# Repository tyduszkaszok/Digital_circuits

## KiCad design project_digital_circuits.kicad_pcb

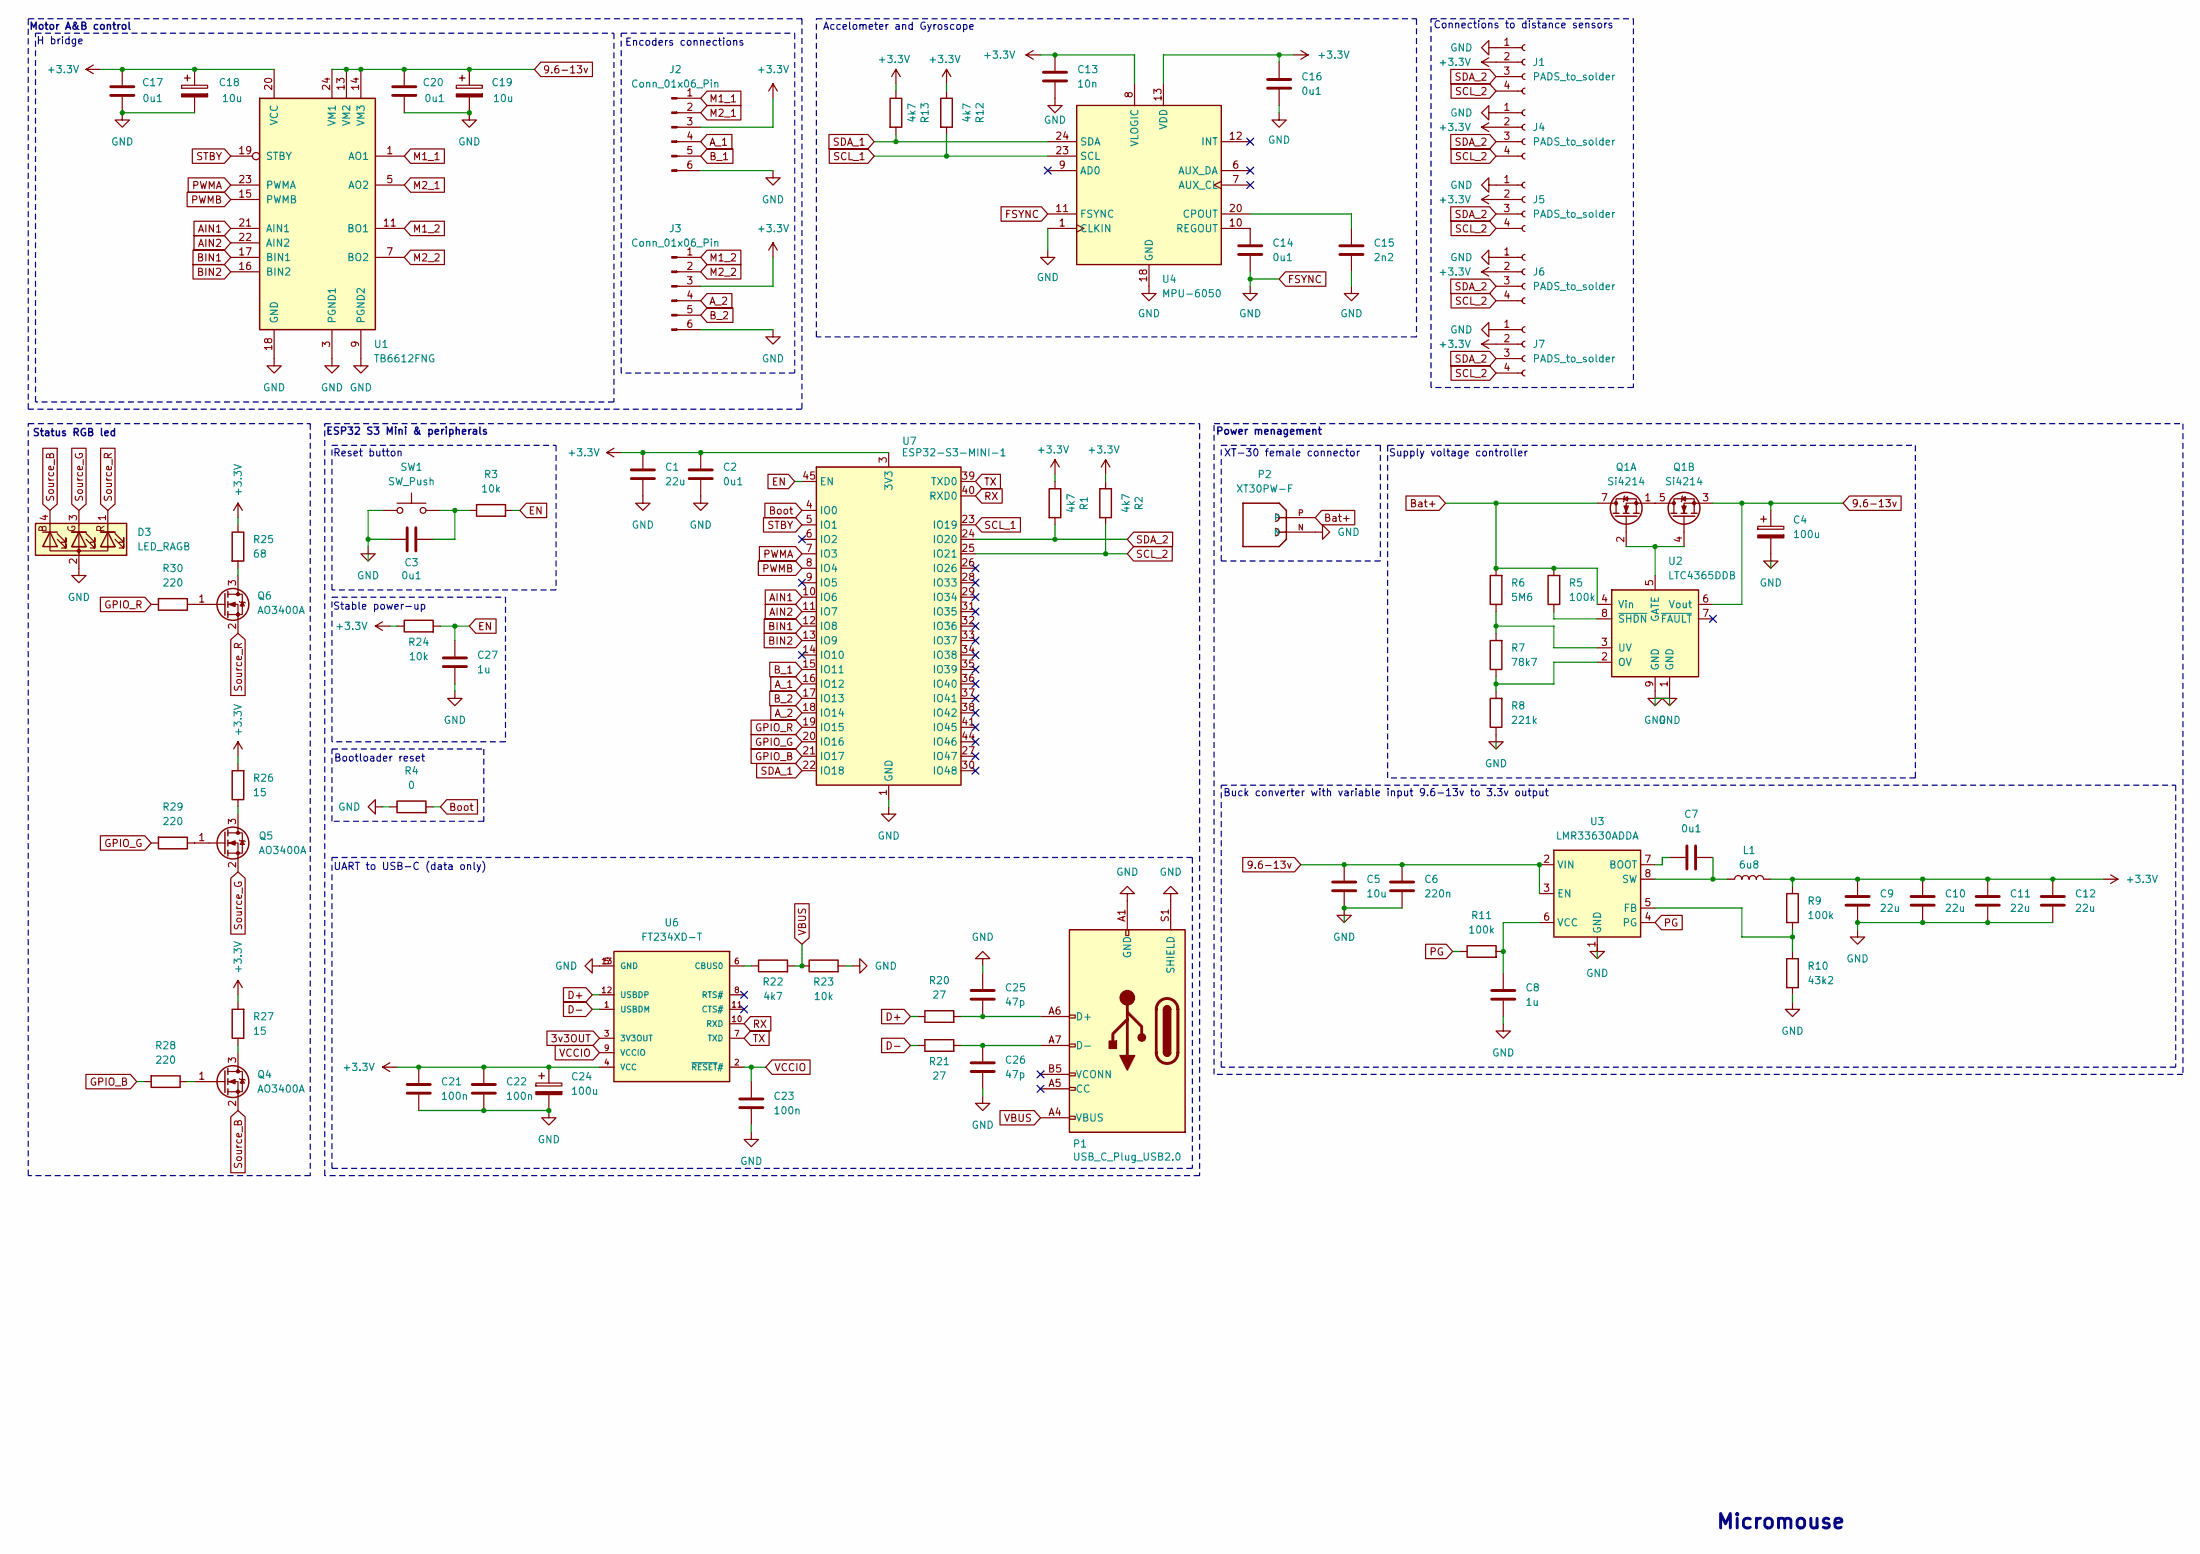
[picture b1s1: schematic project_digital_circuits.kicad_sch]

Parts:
C1, C9, C10, C11, C12: 22u; C_0603_1608Metric
C2, C3, C7, C14, C16, C17, C20: 0u1; C_0603_1608Metric
C4: 100u; CP_Elec_6.3x5.8
C5: 10u; C_0603_1608Metric
C6: 220n; C_0603_1608Metric
C8, C27: 1u; C_0603_1608Metric
C13: 10n; C_0603_1608Metric
C15: 2n2; C_0603_1608Metric
C18, C19: 10u; C_1210_3225Metric
C21, C22, C23: 100n; C_0603_1608Metric
C24: 100u; CP_Elec_5x5.4
C25, C26: 47p; C_0402_1005Metric
D3: LED_RAGB; KAA-3528RGBS-11
J1, J4, J5, J6, J7: PADS_to_solder; SMD_Pad 4x1
J2: Conn_01x06_Pin; SMD_Pad 4x1
J3: Conn_01x06_Pin; SMD_Pad 6x1
L1: 6u8; DR-125
P1: USB_C_Plug_USB2.0; USB_C_Receptacle_GCT_USB4105-xx-A_16P_TopMnt_Horizontal
P2: XT30PW-F; AMASS_XT30PW-F_1x02_P2.50mm_Horizontal; PARTREV 1.2
Q1: Si4214; SOIC-8_3.9x4.9mm_P1.27mm
Q4, Q5, Q6: AO3400A; SOT-23
R1, R2, R12, R13, R22: 4k7; R_0402_1005Metric
R3, R23, R24: 10k; R_0402_1005Metric
R4: 0; R_2010_5025Metric
R5, R9, R11: 100k; R_0402_1005Metric
R6: 5M6; R_0603_1608Metric
R7: 78k7; R_0603_1608Metric
R8: 221k; R_0603_1608Metric
R10: 43k2; R_0402_1005Metric
R20, R21: 27; R_0603_1608Metric
R25: 68; R_1206_3216Metric
R26, R27: 15; R_2010_5025Metric
R28, R29, R30: 220; R_0402_1005Metric
SW1: SW_Push; SW_SPST_Omron_B3FS-100xP
U1: TB6612FNG; SSOP-24_5.3x8.2mm_P0.65mm
U2: LTC4365DDB; DFN-8-1EP_2x3mm_P0.5mm_EP0.61x2.2mm
U3: LMR33630ADDA; Texas_HSOP-8-1EP_3.9x4.9mm_P1.27mm_ThermalVias
U4: MPU-6050; InvenSense_QFN-24_4x4mm_P0.5mm
U6: FT234XD-T; SON45P300X300X80-13N
U7: ESP32-S3-MINI-1; ESP32-S2-MINI-1

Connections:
3v3OUT: U6.3 (3V3OUT)
9.6-13v: C4.1, C5.1, C6.1, C19.1, C20.2, Q1.3 (S2), U1.13 (VM2), U1.14 (VM3), U1.24 (VM1), U2.6 (Vout), U3.2 (VIN), U3.3 (EN)
+3.3V: C1.1, C2.1, C9.1, C10.1, C11.1, C12.1, C13.1, C16.1, C17.2, C18.1, C21.1, C22.1, C24.1, J1.2, J2.3, J3.3, J4.2, J5.2, J6.2, J7.2, L1.2, R1.1, R2.1, R9.1, R12.1, R13.1, R24.1, R25.1, R26.2, R27.2, U1.20 (VCC), U4.8 (VLOGIC), U4.13 (VDD), U6.4 (VCC), U7.3 (3V3)
AIN1: U1.21 (AIN1), U7.10 (IO6)
AIN2: U1.22 (AIN2), U7.11 (IO7)
A_1: J2.4, U7.16 (IO12)
A_2: J3.4, U7.18 (IO14)
BIN1: U1.17 (BIN1), U7.12 (IO8)
BIN2: U1.16 (BIN2), U7.13 (IO9)
B_1: J2.5, U7.15 (IO11)
B_2: J3.5, U7.17 (IO13)
Bat+: P2.P, Q1.7 (D1), Q1.8 (D1), R5.2, R6.2, U2.4 (Vin)
Boot: R4.2, U7.4 (IO0)
D+: R20.1, U6.12 (USBDP)
D-: R21.1, U6.1 (USBDM)
EN: C27.1, R3.2, R24.2, U7.45 (EN)
FSYNC: C1.2, C2.2, C3.2, C4.2, C5.2, C6.2, C8.2, C9.2, C10.2, C11.2, C12.2, C13.2, C14.2, C15.2, C16.2, C17.1, C18.2, C19.2, C20.1, C21.2, C22.2, C23.2, C24.2, C25.1, C26.2, C27.2, D3.2 (A), J1.1, J2.6, J3.6, J4.1, J5.1, J6.1, J7.1, P1.A1 (GND), P1.A12 (GND), P1.B1 (GND), P1.B12 (GND), P1.S1 (SHIELD), P2.N, R4.1, R8.1, R10.2, R23.2, SW1.1, U1.3 (PGND1), U1.4 (PGND1), U1.9 (PGND2), U1.10 (PGND2), U1.18 (GND), U2.1 (GND), U2.9 (GND), U4.1 (CLKIN), U4.11 (FSYNC), U4.18 (GND), U6.5 (GND), U6.13 (GND), U7.1 (GND), U7.2 (GND), U7.42 (GND), U7.43 (GND), U7.46 (GND), U7.47 (GND), U7.48 (GND), U7.49 (GND), U7.50 (GND), U7.51 (GND), U7.52 (GND), U7.53 (GND), U7.54 (GND), U7.55 (GND), U7.56 (GND), U7.57 (GND), U7.58 (GND), U7.59 (GND), U7.60 (GND), U7.61 (GND), U7.62 (GND), U7.63 (GND), U7.64 (GND), U7.65 (GND)
GPIO_B: R28.2, U7.21 (IO17)
GPIO_G: R29.2, U7.20 (IO16)
GPIO_R: R30.2, U7.19 (IO15)
M1_1: J2.1, U1.1 (AO1), U1.2 (AO1)
M1_2: J3.1, U1.11 (BO1), U1.12 (BO1)
M2_1: J2.2, U1.5 (AO2), U1.6 (AO2)
M2_2: J3.2, U1.7 (BO2), U1.8 (BO2)
unnamed: C3.1, R3.1, SW1.2
unnamed: C25.2, P1.A6 (D+), R20.2
unnamed: C26.1, P1.A7 (D-), R21.2
unnamed: Q1.2 (G1), Q1.4 (G2), U2.5 (GATE)
unnamed: Q1.1 (S1), Q1.5 (D2), Q1.6 (D2)
unnamed: Q4.3 (D), R27.1
unnamed: Q4.1 (G), R28.1
unnamed: Q5.3 (D), R26.1
unnamed: Q5.1 (G), R29.1
unnamed: Q6.3 (D), R25.2
unnamed: Q6.1 (G), R30.1
unnamed: R7.1, R8.2, U2.2 (OV)
unnamed: R6.1, R7.2, U2.3 (UV)
unnamed: R5.1, U2.8 (~SHDN)
unnamed: C7.2, U3.7 (BOOT)
unnamed: R9.2, R10.1, U3.5 (FB)
unnamed: U3.1 (GND), U3.9 (GND)
unnamed: C7.1, L1.1, U3.8 (SW)
unnamed: C8.1, R11.2, U3.6 (VCC)
unnamed: C15.1, U4.20 (CPOUT)
unnamed: C14.1, U4.10 (REGOUT)
unnamed: R22.1, U6.6 (CBUS0)
PG: R11.1, U3.4 (PG)
PWMA: U1.23 (PWMA), U7.7 (IO3)
PWMB: U1.15 (PWMB), U7.8 (IO4)
RX: U6.10 (RXD), U7.40 (RXD0)
SCL_1: R12.2, U4.23 (SCL), U7.23 (IO19)
SCL_2: J1.4, J4.4, J5.4, J6.4, J7.4, R2.2, U7.25 (IO21)
SDA_1: R13.2, U4.24 (SDA), U7.22 (IO18)
SDA_2: J1.3, J4.3, J5.3, J6.3, J7.3, R1.2, U7.24 (IO20)
STBY: U1.19 (STBY), U7.5 (IO1)
Source_B: D3.4 (BK), Q4.2 (S)
Source_G: D3.3 (GK), Q5.2 (S)
Source_R: D3.1 (RK), Q6.2 (S)
TX: U6.7 (TXD), U7.39 (TXD0)
VBUS: P1.A4 (VBUS), P1.A9 (VBUS), P1.B4 (VBUS), P1.B9 (VBUS), R22.2, R23.1
VCCIO: C23.1, U6.2 (~RESET#), U6.9 (VCCIO)

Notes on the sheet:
Motor A&B control
Status RGB led
UART to USB-C (data only)
Stable power-up
Supply voltage controller
Micromouse
Accelometer and Gyroscope
Buck converter with variable input 9.6-13v to 3.3v output
Bootloader reset
ESP32 S3 Mini & peripherals
XT-30 female connector
Reset button
H bridge
Connections to distance sensors
Encoders connections
Power menagement

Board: 2 copper layers, 73 parts (0 on the bottom side), 59 nets, no tracks yet.

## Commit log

2024-11-28 test2
2024-11-30 Motor driver added, new symbol for encoder
2024-12-01 ESP-32 added with peripherals with power menagement
2024-12-06 Sensors connections
2024-12-06 Motor driver merged
2024-12-07 Correction of connection UART->USB and Status RGB led added
2024-12-07 Correction and final touches
2024-12-11 final corrections of circuits
2024-12-13 final version of circuits
2024-12-23 Footprints added
2024-12-31 footprints changed
2024-12-31 footprints changed again
